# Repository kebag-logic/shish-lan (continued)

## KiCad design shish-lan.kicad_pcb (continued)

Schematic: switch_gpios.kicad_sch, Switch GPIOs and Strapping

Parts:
J13, J14: SMA; SMA_Right_Angle; MPN RFPC-SMA27-F; Mouser 640-RFPCSMA27F; not fitted
R13, R133: 10K; R_0603; Tolerance_in_pct 5; MPN CRCW060310K0JNEC; Mouser 71-CRCW060310K0JNEC
R17, R25, R92, R126, R127, R128, R129, R135, R136: 0R; R_0603; Tolerance_in_pct 5; MPN RC0603JR-070RP; Mouser 603-RC0603JR-070RP
R18, R21, R22, R93, R98, R119, R130, R131, R132, R134: 0R; R_0603; Tolerance_in_pct 5; MPN RC0603JR-070RP; Mouser 603-RC0603JR-070RP; not fitted
R69: 1K5; R_0603; Tolerance_in_pct 5; MPN AC0603JR-071K5L; Mouser 603-AC0603JR-071K5L
R113, R114, R115, R116, R117, R118: 22R; R_0603; Tolerance_in_pct 1; MPN RC0603FR-1022RL; Mouser 603-RC0603FR-1022RL
TP21, TP22, TP24, TP25, TP26, TP27: TestPoint
U1: LAN96455F-I/8MW; TQFP-128_14x14mm_P0.4mm; MPN LAN96455F-I/8MW; Mouser 579-LAN96455FI8MW

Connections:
/controller/MIIM0_STM_SWITCH.SLV_MDC: R17.1; also elsewhere on the board
/controller/MIIM0_STM_SWITCH.SLV_MDIO: R25.1; also elsewhere on the board
/controller/RGMII0_SWITCH_STM.RXCTL-CRS_DV: U1.74 (GPIO_21/RGMII0_RXCTL-CRS_DV); also elsewhere on the board
/controller/RGMII0_SWITCH_STM.RXD0: U1.80 (GPIO_16/RGMII0_RXD0); also elsewhere on the board
/controller/RGMII0_SWITCH_STM.RXD1: U1.79 (GPIO_17/RGMII0_RXD1); also elsewhere on the board
/controller/RGMII0_SWITCH_STM.RXD2: U1.78 (GPIO_18/RGMII0_RXD2-RXER); also elsewhere on the board
/controller/RGMII0_SWITCH_STM.RXD3: U1.76 (GPIO_19/RGMII0_RXD3); also elsewhere on the board
/controller/RGMII0_SWITCH_STM.RX_CLK: U1.75 (GPIO_20/RGMII0_RXC-REFCLK); also elsewhere on the board
/controller/RGMII0_SWITCH_STM.TXC-REFCLK: R118.1; also elsewhere on the board
/controller/RGMII0_SWITCH_STM.TXCTL-DX_DV: R117.1; also elsewhere on the board
/controller/RGMII0_SWITCH_STM.TXD0: R116.1; also elsewhere on the board
/controller/RGMII0_SWITCH_STM.TXD1: R115.1; also elsewhere on the board
/controller/RGMII0_SWITCH_STM.TXD2: R114.1; also elsewhere on the board
/controller/RGMII0_SWITCH_STM.TXD3: R113.1; also elsewhere on the board
/controller/SPI2_STM_SWITCH.CLK: R18.1, TP27.1 (1_1); also elsewhere on the board
/controller/SPI2_STM_SWITCH.MISO: R22.1, TP25.1 (1_1); also elsewhere on the board
/controller/SPI2_STM_SWITCH.MOSI: R21.1, TP24.1 (1_1); also elsewhere on the board
/controller/SPI2_STM_SWITCH.nCS: TP26.1 (1_1), U1.98 (GPIO_2/SI_nCS/SI_SLV_nCS/I2C1_SDA/-/-/-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); also elsewhere on the board
/switch/IRQ0_SWITCH_TO_STM: R92.1; also elsewhere on the board
/switch/switch_gpios/BOOT_MODE0: R116.2, U1.70 (GPIO_24/RGMII0_TXD0/-/-/-/-/-/-|BOOT_MO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); also elsewhere on the board
/switch/switch_gpios/BOOT_MODE1: R115.2, U1.68 (GPIO_25/RGMII0_TXD1/-/-/-/-/-/-|BOOT_MO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); also elsewhere on the board
/switch/switch_gpios/BOOT_MODE2: R114.2, U1.67 (GPIO_26/RGMII0_TXD2/-/-/-/-/-/-|BOOT_MO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); also elsewhere on the board
/switch/switch_gpios/CUPHY_MODE: U1.82 (GPIO_14/RGMII1_TXD2/I2C0_SCL12/-/PTP2/-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); also elsewhere on the board
/switch/switch_gpios/E2E_CLOCK_EN: U1.87 (GPIO_10/RGMII1_TXC-REFCLK/I2C0_SCL8/RCL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); also elsewhere on the board
/switch/switch_gpios/EEE_EN: R98.2, U1.85 (GPIO_12/RGMII1_TXD0/I2C0_SCL10/MIIM1_MD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); also elsewhere on the board
/switch/switch_gpios/EEPROM_SIZE: R92.2, R93.2, U1.60 (GPIO_33/PTP3/IRQ0/|EEPROM_SIZE); also elsewhere on the board
/switch/switch_gpios/FLOW_EN: U1.86 (GPIO_11/RGMII1_TXCTL-TX_DV/I2C0_SCL9/MI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); also elsewhere on the board
/switch/switch_gpios/GPIO_MODE0: R126.2, U1.41 (GPIO_36/PTP0/PHY3_LED0/PHY2_LED0/-/MAC_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); also elsewhere on the board
/switch/switch_gpios/GPIO_MODE1: R127.2, U1.40 (GPIO_37/PTP1/PHY3_LED1/PHY1_LED0/-/MAC_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); also elsewhere on the board
/switch/switch_gpios/JTAG_ENB: U1.43 (GPIO_34/RCLK0/PHY4_LED0/PHY4_LED0/-/-/-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); also elsewhere on the board
/switch/switch_gpios/JTAG_SWITCH.TCK: R131.1
/switch/switch_gpios/JTAG_SWITCH.TDI: R130.1
/switch/switch_gpios/JTAG_SWITCH.TDO: R132.1
/switch/switch_gpios/JTAG_SWITCH.TMS: R134.1
/switch/switch_gpios/LED_MODE: U1.83 (GPIO_13/RGMII1_TXD1/I2C0_SCL11/-/PTP1/M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); also elsewhere on the board
/switch/switch_gpios/LOOP_EN: U1.42 (GPIO_35/RCLK1/PHY4_LED1/PHY3_LED0/-/MAC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); also elsewhere on the board
/switch/switch_gpios/MGMT_MODE0: R113.2, U1.66 (GPIO_27/RGMII0_TXD3/-/-/-/-/-/-|MGMT_MO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); also elsewhere on the board
/switch/switch_gpios/MGMT_MODE1: R119.2, U1.65 (GPIO_28/RCLK0/MIIM0_MDC/-/-/-/-/-|MGMT_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); also elsewhere on the board
/switch/switch_gpios/PHY0_LED0: R133.2, U1.33 (GPIO_42/SI_nCS/PHY0_LED0/SG0_DI/IRQ2/MA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); also elsewhere on the board
/switch/switch_gpios/PHY0_LED1: R134.2, U1.31 (GPIO_43/SI_CLK/PHY0_LED1/SG0_LD/IRQ3/MA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); also elsewhere on the board
/switch/switch_gpios/PHY1_LED0: R136.1; also elsewhere on the board
/switch/switch_gpios/PHY1_LED1: R135.1; also elsewhere on the board
/switch/switch_gpios/PHY2_LED0: R128.1; also elsewhere on the board
/switch/switch_gpios/PHY2_LED1: R129.1; also elsewhere on the board
/switch/switch_gpios/PHY3_LED0: R126.1; also elsewhere on the board
/switch/switch_gpios/PHY3_LED1: R127.1; also elsewhere on the board
/switch/switch_gpios/PTP0: J14.1 (In), U1.63 (GPIO_30/PTP0/I2C0_SDA/UART_RXD/-/-/-/-)
/switch/switch_gpios/PTP1: U1.62 (GPIO_31/PTP1/I2C0_SCL0/UART_TXD/-/-/-/-)
/switch/switch_gpios/PTP2: U1.61 (GPIO_32/PTP2/I2C0_SCL1/-/-/-/-/-)
/switch/switch_gpios/PTP3: R93.1
/switch/switch_gpios/SD_125M: R117.2, U1.71 (GPIO_23/RGMII0_TXCTL-TX_DV/-/-/-/-/-/-|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); also elsewhere on the board
/switch/switch_gpios/SD_MODE0: R129.2, R130.2, U1.36 (GPIO_39/UART_TXD/PHY2_LED1/-/-/MAC_LED4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); also elsewhere on the board
/switch/switch_gpios/SD_MODE1: R131.2, R136.2, U1.35 (GPIO_40/SI_DI/PHY1_LED0/SG0_CLK/-/MAC_L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); also elsewhere on the board
/switch/switch_gpios/SFP_EN: U1.81 (GPIO_15/RGMII1_TXD3/I2C0_SCL13/-/PTP3/-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); also elsewhere on the board
/switch/switch_gpios/SGPIO_EN: R118.2, U1.72 (GPIO_22/RGMII0_TXC-REFCLK/-/-/-/-/-/-|G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); also elsewhere on the board
/switch/switch_gpios/SYNCE_0: R119.1; also elsewhere on the board
/switch/switch_gpios/SYNCE_1: U1.64 (GPIO_29/RCLK1/MIIM0_MDIO/-/-/-/-/-); also elsewhere on the board
/switch/switch_gpios/XMII_MODE0: R132.2, R135.2, U1.34 (GPIO_41/SI_DO/PHY1_LED1/SG0_DO/IRQ1/MAC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); also elsewhere on the board
/switch/switch_gpios/XMII_MODE1: R128.2, U1.38 (GPIO_38/-/PHY2_LED0/PHY0_LED0/-/MAC_LED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); also elsewhere on the board
unnamed: J13.1 (In), R98.1
unnamed: R13.1, R21.2, U1.100 (GPIO_0/SI_DI/SI_SLV_DI/I2C_SLV_SDA/MIIM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)
unnamed: R17.2, R22.2, TP21.1 (1_1), U1.99 (GPIO_1/SI_DO/SI_SLV_DO/I2C_SLV_SCL/MIIM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)
unnamed: R18.2, R25.2, R69.2, TP22.1 (1_1), U1.97 (GPIO_3/SI_CLK//SI_SLV_CLK/I2C1_SCL/MIIM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)

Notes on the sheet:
Checklist * Pinouts [ AM 2026-12-21 OK ] * Element correctness (KL) [ AM 2026-12-21 OK ] * Connections [ AM 2026-12-21 OK ]
We leave the option to use either the SPI or the MDIO bus. If the MDIO is used, remove R69 and R13.

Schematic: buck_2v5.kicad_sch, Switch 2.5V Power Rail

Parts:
C96, C100: 10u; C_0603; Voltage_in_V 25; Tolerance_in_pct 20; MPN CL10A106MA8NRNC; Mouser 187-CL10A106MA8NRNC; not fitted
C97, C101, C102, C107, C108: 10u; C_0603; Voltage_in_V 25; Tolerance_in_pct 20; MPN CL10A106MA8NRNC; Mouser 187-CL10A106MA8NRNC
C99: 10p; C_0603; Voltage_in_V 25; Tolerance_in_pct 5; MPN CC0603JRNPO8BN100; Mouser 603-CC0603JRNP8BN100
C103: 10n; C_0603; Voltage_in_V 50; Tolerance_in_pct 10; MPN CL10B103KB8WPND; Mouser 187-CL10B103KB8WPND; not fitted
D2: LED_{color}_{U_F}_{I_F}; LED_0603; MPN LTST-C194KRKT; Mouser 859-LTST-C194KRKT
J17: Header_02x01_2.54mm_0mm_Straight; 02x01_2.54mm_Header; MPN 87224-2; Mouser 571-872242
L3: 3u3; EXLA1V0603; Tolerance_in_pct 20; MPN EXLA1V0603-3R3-R; Digikey 283-EXLA1V0603-3R3-RCT-ND
R19: 31K6; R_0603; Tolerance_in_pct 1; MPN CRCW060331K6FKEA; Mouser 71-CRCW0603-31.6K-E3
R85: 10K; R_0603; Tolerance_in_pct 1; MPN RC0603FR-0710KL; Mouser 603-RC0603FR-0710KL
R95: 1K5; R_0603; Tolerance_in_pct 5; MPN AC0603JR-071K5L; Mouser 603-AC0603JR-071K5L
R99: 10K; R_0603; Tolerance_in_pct 5; MPN CRCW060310K0JNEC; Mouser 71-CRCW060310K0JNEC; not fitted
TP28, TP29, TP30, TP31: TestPoint
U3: TPS564257DRLR; SOT-563; MPN TPS564257DRLR; Mouser 595-TPS564257DRLR

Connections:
/5-12V_INPUT: C100.1, C101.1, C102.1, TP29.1 (1_1), U3.1 (VIN); also elsewhere on the board
/switch/2V5_BUCK-OUT: C96.1, C97.1, C107.1, J17.1, TP28.1 (1_1); also elsewhere on the board
unnamed: D2.2 (A), R95.2
unnamed: D2.1 (K), TP30.1 (1_1), U3.4 (PG)
unnamed: C99.1, C108.1, J17.2, L3.2, R19.1
unnamed: C99.2, R19.2, R85.1, U3.6 (FB)
unnamed: L3.1, U3.2 (SW)

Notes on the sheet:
Based on WEBENCH design: https://drive.google.com/file/d/1STtModBE37J_lW2Zfq6PtjpJq2d4hOYi/view?usp=drive_link
Checklist * Pinouts [ AM OK - 2026-12-21 ] * Element correctness [ AM OK - 2026-12-21 ] * Connections [ AM OK - 2026-12-21 ]
Documentation found here: https://www.ti.com/product/TPS564257
Generation of the 2.5V for PHYs

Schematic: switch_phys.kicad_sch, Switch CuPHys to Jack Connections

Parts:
R70: 6K04; R_0603; Tolerance_in_pct 1; MPN RMCF0603FT6K04; Mouser 708-RMCF0603FT6K04
U1: LAN96455F-I/8MW; TQFP-128_14x14mm_P0.4mm; MPN LAN96455F-I/8MW; Mouser 579-LAN96455FI8MW

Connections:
/switch/switch_phys/RJ45_Connector_Port0/TRD1+_0: U1.102 (P0.A_P); also elsewhere on the board
/switch/switch_phys/RJ45_Connector_Port0/TRD1-_0: U1.103 (P0.A_N); also elsewhere on the board
/switch/switch_phys/RJ45_Connector_Port0/TRD2+_0: U1.105 (P0.B_P); also elsewhere on the board
/switch/switch_phys/RJ45_Connector_Port0/TRD2-_0: U1.106 (P0.B_N); also elsewhere on the board
/switch/switch_phys/RJ45_Connector_Port0/TRD3+_0: U1.108 (P0.C_P); also elsewhere on the board
/switch/switch_phys/RJ45_Connector_Port0/TRD3-_0: U1.109 (P0.C_N); also elsewhere on the board
/switch/switch_phys/RJ45_Connector_Port0/TRD4+_0: U1.110 (P0.D_P); also elsewhere on the board
/switch/switch_phys/RJ45_Connector_Port0/TRD4-_0: U1.111 (P0.D_N); also elsewhere on the board
/switch/switch_phys/RJ45_Connector_Port1/TRD1+_1: U1.112 (P1.A_P); also elsewhere on the board
/switch/switch_phys/RJ45_Connector_Port1/TRD1-_1: U1.113 (P1.A_N); also elsewhere on the board
/switch/switch_phys/RJ45_Connector_Port1/TRD2+_1: U1.114 (P1.B_P); also elsewhere on the board
/switch/switch_phys/RJ45_Connector_Port1/TRD2-_1: U1.115 (P1.B_N); also elsewhere on the board
/switch/switch_phys/RJ45_Connector_Port1/TRD3+_1: U1.117 (P1.C_P); also elsewhere on the board
/switch/switch_phys/RJ45_Connector_Port1/TRD3-_1: U1.118 (P1.C_N); also elsewhere on the board
/switch/switch_phys/RJ45_Connector_Port1/TRD4+_1: U1.120 (P1.D_P); also elsewhere on the board
/switch/switch_phys/RJ45_Connector_Port1/TRD4-_1: U1.121 (P1.D_N); also elsewhere on the board
/switch/switch_phys/RJ45_Connector_Port2/TRD1+_2: U1.1 (P2.A_P); also elsewhere on the board
/switch/switch_phys/RJ45_Connector_Port2/TRD1-_2: U1.2 (P2.A_N); also elsewhere on the board
/switch/switch_phys/RJ45_Connector_Port2/TRD2+_2: U1.4 (P2.B_P); also elsewhere on the board
/switch/switch_phys/RJ45_Connector_Port2/TRD2-_2: U1.5 (P2.B_N); also elsewhere on the board
/switch/switch_phys/RJ45_Connector_Port2/TRD3+_2: U1.7 (P2.C_P); also elsewhere on the board
/switch/switch_phys/RJ45_Connector_Port2/TRD3-_2: U1.8 (P2.C_N); also elsewhere on the board
/switch/switch_phys/RJ45_Connector_Port2/TRD4+_2: U1.9 (P2.D_P); also elsewhere on the board
/switch/switch_phys/RJ45_Connector_Port2/TRD4-_2: U1.10 (P2.D_N); also elsewhere on the board
/switch/switch_phys/RJ45_Connector_Port3/TRD1+_3: U1.11 (P3.A_P); also elsewhere on the board
/switch/switch_phys/RJ45_Connector_Port3/TRD1-_3: U1.12 (P3.A_N); also elsewhere on the board
/switch/switch_phys/RJ45_Connector_Port3/TRD2+_3: U1.13 (P3.B_P); also elsewhere on the board
/switch/switch_phys/RJ45_Connector_Port3/TRD2-_3: U1.14 (P3.B_N); also elsewhere on the board
/switch/switch_phys/RJ45_Connector_Port3/TRD3+_3: U1.17 (P3.C_P); also elsewhere on the board
/switch/switch_phys/RJ45_Connector_Port3/TRD3-_3: U1.18 (P3.C_N); also elsewhere on the board
/switch/switch_phys/RJ45_Connector_Port3/TRD4+_3: U1.19 (P3.D_P); also elsewhere on the board
/switch/switch_phys/RJ45_Connector_Port3/TRD4-_3: U1.20 (P3.D_N); also elsewhere on the board
unnamed: R70.1, U1.127 (ISET)

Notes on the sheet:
Checklist * Pinouts [ AM OK - 2026-12-21 ] * Element correctness [ AM OK - 2026-12-21 ] * Connections [ AM OK - 2026-12-21 ]
The assumption, for the LEDS is that the VDD_IO will be 3.3V not 1.8V, not 2.5V

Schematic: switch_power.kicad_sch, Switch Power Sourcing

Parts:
C1, C18, C19, C20, C21: 100n; C_0603; Voltage_in_V 50; Tolerance_in_pct 10; MPN CL10B104KB8NNNC; Mouser 187-CL10B104KB8NNNC
C106: 10n; C_0603; Voltage_in_V 50; Tolerance_in_pct 10; MPN CL10B103KB8WPND; Mouser 187-CL10B103KB8WPND; not fitted
FB1, FB2, FB3, FB4, FB5: 33R; FB_0603; MPN BLM18PG330SN1D; Mouser 81-BLM18PG330SN1D
R71: 10R; R_0603; Tolerance_in_pct 0.1; MPN RNCE0603BTE10R0; Mouser 708-RNCE0603BTE10R0
R72, R73: 0R; R_0603; Tolerance_in_pct 5; MPN RC0603JR-070RP; Mouser 603-RC0603JR-070RP
R81: 10K; R_0603; Tolerance_in_pct 5; MPN CRCW060310K0JNEC; Mouser 71-CRCW060310K0JNEC
R88, R120, R121: 0R; R_2512; Tolerance_in_pct 5; MPN CRF2512-J/-000ELF; Mouser 652-CRF2512-J-000ELF; not fitted
TP4, TP5, TP6, TP7, TP8, TP9, TP19, TP20: TestPoint
U1: LAN96455F-I/8MW; TQFP-128_14x14mm_P0.4mm; MPN LAN96455F-I/8MW; Mouser 579-LAN96455FI8MW

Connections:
/switch/1V15_BUCK-OUT: R121.1; also elsewhere on the board
/switch/2V5_BUCK-OUT: R120.1; also elsewhere on the board
/switch/nRST_STM_TO_SWITCH: C106.1, R81.1, TP20.1 (1_1), U1.101 (nRST); also elsewhere on the board
/switch/switch_power/1V15_PWR_SWITCH: C19.1, C20.1, FB1.1, FB2.1, FB3.1, R121.2, TP8.1 (1_1), U1.37 (VDD), U1.59 (VDD), U1.73 (VDD), U1.88 (VDD), U1.122 (VDD); also elsewhere on the board
/switch/switch_power/2V5_PWR_SWITCH: C1.1, C18.1, FB4.1, FB5.1, R120.2
/switch/switch_power/VDDIO: R88.2, U1.32 (VDD_IO_E), U1.39 (VDD_IO_E), U1.58 (VDD_IO_D), U1.69 (VDD_IO_C), U1.77 (VDD_IO_C), U1.84 (VDD_IO_B), U1.92 (VDD_IO_B), U1.96 (VDD_IO_A); also elsewhere on the board
/switch/switch_power/VDDIO_PHY_AH: FB4.2, TP6.1 (1_1), U1.6 (VDD_AH), U1.16 (VDD_AH), U1.25 (VDD_AH), U1.107 (VDD_AH), U1.116 (VDD_AH), U1.128 (VDD_AH); also elsewhere on the board
/switch/switch_power/VDDIO_PHY_AHS: FB5.2, TP7.1 (1_1), U1.44 (VDD_AHS), U1.52 (VDD_AHS); also elsewhere on the board
/switch/switch_power/VDD_PHYS: FB3.2, TP4.1 (1_1), U1.3 (VDD_AL), U1.15 (VDD_AL), U1.28 (VDD_AL), U1.104 (VDD_AL), U1.119 (VDD_AL); also elsewhere on the board
/switch/switch_power/VDD_SERDES: FB2.2, TP5.1 (1_1), U1.47 (VDD_ALS0), U1.54 (VDD_ALS1); also elsewhere on the board
/switch/switch_power/xtal_switch/Pin1: R73.1, TP9.1 (1_1); also elsewhere on the board
/switch/switch_power/xtal_switch/Pin2: R72.1, TP19.1 (1_1); also elsewhere on the board
unnamed: FB1.2, R71.1
unnamed: C21.2, U1.125 (RTN_PLL)
unnamed: C21.1, R71.2, U1.126 (VDD_PLL)
unnamed: R73.2, U1.124 (XI)
unnamed: R72.2, U1.123 (XO)

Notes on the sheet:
WARNING: Make sure that the LEDS in the PHY part are connected to the right power
The voltage selected (2.5V or 3.3V) must also be used on the VDD_AHS supply.
Checklist * Pinouts [ AM OK - 2026-12-21 ] * Element correctness [ AM OK - 2026-12-21 ] * Connections [ AM OK - 2026-12-21 ]
VDD on the Domain D has to be 3.3V

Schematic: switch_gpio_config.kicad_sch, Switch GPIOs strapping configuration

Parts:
R14, R35, R37, R41, R44, R52, R56, R68: 10K; R_0603; Tolerance_in_pct 5; MPN CRCW060310K0JNEC; Mouser 71-CRCW060310K0JNEC
R26, R27, R28, R29, R30, R31, R32, R33, R34, R36, R38, R39, R40, R42, R43, R45, R46, R47, R48, R49, R50, R51, R53, R54, R55, R57, R58, R59, R60, R61, R62, R63, R64, R65, R66, R67: 10K; R_0603; Tolerance_in_pct 5; MPN CRCW060310K0JNEC; Mouser 71-CRCW060310K0JNEC; not fitted

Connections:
/switch/switch_gpios/BOOT_MODE0: R30.2, R52.1; also elsewhere on the board
/switch/switch_gpios/BOOT_MODE1: R34.2, R68.1; also elsewhere on the board
/switch/switch_gpios/BOOT_MODE2: R35.1, R65.2; also elsewhere on the board
/switch/switch_gpios/CUPHY_MODE: R40.2, R60.1; also elsewhere on the board
/switch/switch_gpios/E2E_CLOCK_EN: R47.2, R51.1; also elsewhere on the board
/switch/switch_gpios/EEE_EN: R49.1, R58.2; also elsewhere on the board
/switch/switch_gpios/EEPROM_SIZE: R42.1, R63.2; also elsewhere on the board
/switch/switch_gpios/FLOW_EN: R45.2, R64.1; also elsewhere on the board
/switch/switch_gpios/GPIO_MODE0: R39.1, R57.2; also elsewhere on the board
/switch/switch_gpios/GPIO_MODE1: R38.1, R59.2; also elsewhere on the board
/switch/switch_gpios/JTAG_ENB: R41.2, R53.1; also elsewhere on the board
/switch/switch_gpios/LED_MODE: R48.2, R50.1; also elsewhere on the board
/switch/switch_gpios/LOOP_EN: R28.1, R43.2; also elsewhere on the board
/switch/switch_gpios/MGMT_MODE0: R55.2, R56.1; also elsewhere on the board
/switch/switch_gpios/MGMT_MODE1: R14.2, R54.1; also elsewhere on the board
/switch/switch_gpios/SD_125M: R37.1, R67.2; also elsewhere on the board
/switch/switch_gpios/SD_MODE0: R29.2, R31.1; also elsewhere on the board
/switch/switch_gpios/SD_MODE1: R33.1, R36.2; also elsewhere on the board
/switch/switch_gpios/SFP_EN: R46.1, R61.2; also elsewhere on the board
/switch/switch_gpios/SGPIO_EN: R44.1, R62.2; also elsewhere on the board
/switch/switch_gpios/XMII_MODE0: R26.2, R66.1; also elsewhere on the board
/switch/switch_gpios/XMII_MODE1: R27.2, R32.1; also elsewhere on the board

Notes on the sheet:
*0: Disable EEE on CuPHY ports 1: Enable EEE on CuPHY ports
MANAGED CONFIGURATION STRAPS
*0: GPIOs will be used to control SFP signals 1: SGPIOS will be used to control SFP signals
Enables a 125 MHz reference clock input to SerDes Note: If SD_125M is strapped high, SGPIO_EN must be strapped low.
0: Single color mode (one LED signaling link-up and one led signaling activity) *1: Tri-color mode (two LEDs to indicate link-up with different color depending on link speed, LEDs blinking with activity)
*0: 16-bit addressing 1: 8-bit addressing
Management Interface Mode Selector 0: UART CLI 1: I2C client *2: MIIM client 3: SPI client
*0: Disable flow control 1: Enable flow control
*0: SGMII (1G, 2.5G) 1: SFP (-X, -KX, -FX)
*0: Disable end-to-end transparent clock 1: Enable end-to-end transparent clock
0: Auto negotiation, Auto MDI-X - all advertised *1: Auto negotiation, Auto MDI-X - 100FD/HD, 10FD/HD advertised
*0: Disable loop prevention 1: Enable loop prevention
Note: If JTAG is enabled, configuration strap BOOT_MODE0 selects: 0: DFT TAP controller 1: SerDes TAP controller 0: Enable JTAG *1: Disable JTAG
Each strap number controls a corresponding RGMII interface number. 0: RGMII *1: RMII
*0: Disable 2.5G detect 1: Enable 2.5G detect
0: Mode A (2x RGMII, 1-2x SGMII) 1: Mode B (1x QSGMII, 0x SGMII, 0-1x RGMII) 2: Mode C (2x RGMII, 0x SGMII) *3: Mode D (0-1x RGMII, 0-2x SGMII)
Boot Mode Selector Note: Unmanaged modes are selected using options 3, 4, 5, 6, or 7. *0: [Managed] No boot --> Need management interface to work 1: RESERVED 2: RESERVED 3: [Unmanaged] ROM boot. 4: [Unmanaged] ROM + I2C table boot. 5: [Unmanaged] ROM + SPI table boot. 6: [Unmanaged] ROM + VRAP port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

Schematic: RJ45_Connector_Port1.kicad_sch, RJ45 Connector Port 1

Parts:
C3, C8, C9, C10: 100n; C_0603; Voltage_in_V 50; Tolerance_in_pct 10; MPN CL10B104KB8NNNC; Mouser 187-CL10B104KB8NNNC
J1: RJ45_0826-1X4T-43-F; BEL_0826-1X4T-43-F; MPN 0826-1X4T-43-F; Mouser 530-0826-1X4T-43-F
R1, R2, R11: 1K; R_0603; Tolerance_in_pct 5; MPN CRGCQ0603J1K0; Mouser 279-CRGCQ0603J1K0

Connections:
/switch/switch_gpios/PHY1_LED0: R2.1; also elsewhere on the board
/switch/switch_gpios/PHY1_LED1: J1.15_2; also elsewhere on the board
/switch/switch_phys/RJ45_Connector_Port1/TRD1+_1: J1.11_2 (TRD1+_2); also elsewhere on the board
/switch/switch_phys/RJ45_Connector_Port1/TRD1-_1: J1.10_2 (TRD1-_2); also elsewhere on the board
/switch/switch_phys/RJ45_Connector_Port1/TRD2+_1: J1.4_2 (TRD2+_2); also elsewhere on the board
/switch/switch_phys/RJ45_Connector_Port1/TRD2-_1: J1.5_2 (TRD2-_2); also elsewhere on the board
/switch/switch_phys/RJ45_Connector_Port1/TRD3+_1: J1.3_2 (TRD3+_2); also elsewhere on the board
/switch/switch_phys/RJ45_Connector_Port1/TRD3-_1: J1.2_2 (TRD3-_2); also elsewhere on the board
/switch/switch_phys/RJ45_Connector_Port1/TRD4+_1: J1.8_2 (TRD4+_2); also elsewhere on the board
/switch/switch_phys/RJ45_Connector_Port1/TRD4-_1: J1.9_2 (TRD4-_2); also elsewhere on the board
unnamed: J1.13_2, R2.2
unnamed: J1.16_2, R1.2, R11.1
unnamed: C3.2, J1.12_2 (TRCT1_2)
unnamed: C8.2, J1.6_2 (TRCT2_2)
unnamed: C9.2, J1.1_2 (TRCT3_2)
unnamed: C10.2, J1.7_2 (TRCT4_2)

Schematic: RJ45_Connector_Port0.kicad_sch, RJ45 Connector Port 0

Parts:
C4, C5, C6, C7: 100n; C_0603; Voltage_in_V 50; Tolerance_in_pct 10; MPN CL10B104KB8NNNC; Mouser 187-CL10B104KB8NNNC
J1: RJ45_0826-1X4T-43-F; BEL_0826-1X4T-43-F; MPN 0826-1X4T-43-F; Mouser 530-0826-1X4T-43-F
R5, R6, R7: 1K; R_0603; Tolerance_in_pct 5; MPN CRGCQ0603J1K0; Mouser 279-CRGCQ0603J1K0

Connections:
/switch/switch_gpios/PHY0_LED0: R6.1; also elsewhere on the board
/switch/switch_gpios/PHY0_LED1: J1.15_1; also elsewhere on the board
/switch/switch_phys/RJ45_Connector_Port0/TRD1+_0: J1.11_1 (TRD1+_1); also elsewhere on the board
/switch/switch_phys/RJ45_Connector_Port0/TRD1-_0: J1.10_1 (TRD1-_1); also elsewhere on the board
/switch/switch_phys/RJ45_Connector_Port0/TRD2+_0: J1.4_1 (TRD2+_1); also elsewhere on the board
/switch/switch_phys/RJ45_Connector_Port0/TRD2-_0: J1.5_1 (TRD2-_1); also elsewhere on the board
/switch/switch_phys/RJ45_Connector_Port0/TRD3+_0: J1.3_1 (TRD3+_1); also elsewhere on the board
/switch/switch_phys/RJ45_Connector_Port0/TRD3-_0: J1.2_1 (TRD3-_1); also elsewhere on the board
/switch/switch_phys/RJ45_Connector_Port0/TRD4+_0: J1.8_1 (TRD4+_1); also elsewhere on the board
/switch/switch_phys/RJ45_Connector_Port0/TRD4-_0: J1.9_1 (TRD4-_1); also elsewhere on the board
unnamed: J1.13_1, R6.2
unnamed: J1.16_1, R5.2, R7.1
unnamed: C4.2, J1.12_1 (TRCT1_1)
unnamed: C5.2, J1.6_1 (TRCT2_1)
unnamed: C6.1, J1.1_1 (TRCT3_1)
unnamed: C7.2, J1.7_1 (TRCT4_1)

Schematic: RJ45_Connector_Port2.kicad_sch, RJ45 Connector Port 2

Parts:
C11, C12, C13, C14: 100n; C_0603; Voltage_in_V 50; Tolerance_in_pct 10; MPN CL10B104KB8NNNC; Mouser 187-CL10B104KB8NNNC
J1: RJ45_0826-1X4T-43-F; BEL_0826-1X4T-43-F; MPN 0826-1X4T-43-F; Mouser 530-0826-1X4T-43-F
R3, R4, R8: 1K; R_0603; Tolerance_in_pct 5; MPN CRGCQ0603J1K0; Mouser 279-CRGCQ0603J1K0

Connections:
/switch/switch_gpios/PHY2_LED0: R3.1; also elsewhere on the board
/switch/switch_gpios/PHY2_LED1: J1.15_3; also elsewhere on the board
/switch/switch_phys/RJ45_Connector_Port2/TRD1+_2: J1.11_3 (TRD1+_3); also elsewhere on the board
/switch/switch_phys/RJ45_Connector_Port2/TRD1-_2: J1.10_3 (TRD1-_3); also elsewhere on the board
/switch/switch_phys/RJ45_Connector_Port2/TRD2+_2: J1.4_3 (TRD2+_3); also elsewhere on the board
/switch/switch_phys/RJ45_Connector_Port2/TRD2-_2: J1.5_3 (TRD2-_3); also elsewhere on the board
/switch/switch_phys/RJ45_Connector_Port2/TRD3+_2: J1.3_3 (TRD3+_3); also elsewhere on the board
/switch/switch_phys/RJ45_Connector_Port2/TRD3-_2: J1.2_3 (TRD3-_3); also elsewhere on the board
/switch/switch_phys/RJ45_Connector_Port2/TRD4+_2: J1.8_3 (TRD4+_3); also elsewhere on the board
/switch/switch_phys/RJ45_Connector_Port2/TRD4-_2: J1.9_3 (TRD4-_3); also elsewhere on the board
unnamed: J1.13_3, R3.2
unnamed: J1.16_3, R4.1, R8.2
unnamed: C11.1, J1.12_3 (TRCT1_3)
unnamed: C12.2, J1.6_3 (TRCT2_3)
unnamed: C13.2, J1.1_3 (TRCT3_3)
unnamed: C14.2, J1.7_3 (TRCT4_3)

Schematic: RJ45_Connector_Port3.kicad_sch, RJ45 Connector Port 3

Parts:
C2, C15, C16, C17: 100n; C_0603; Voltage_in_V 50; Tolerance_in_pct 10; MPN CL10B104KB8NNNC; Mouser 187-CL10B104KB8NNNC
J1: RJ45_0826-1X4T-43-F; BEL_0826-1X4T-43-F; MPN 0826-1X4T-43-F; Mouser 530-0826-1X4T-43-F
R9, R10, R12: 1K; R_0603; Tolerance_in_pct 5; MPN CRGCQ0603J1K0; Mouser 279-CRGCQ0603J1K0

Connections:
/switch/switch_gpios/PHY3_LED0: R12.1; also elsewhere on the board
/switch/switch_gpios/PHY3_LED1: J1.15_4; also elsewhere on the board
/switch/switch_phys/RJ45_Connector_Port3/TRD1+_3: J1.11_4 (TRD1+_4); also elsewhere on the board
/switch/switch_phys/RJ45_Connector_Port3/TRD1-_3: J1.10_4 (TRD1-_4); also elsewhere on the board
/switch/switch_phys/RJ45_Connector_Port3/TRD2+_3: J1.4_4 (TRD2+_4); also elsewhere on the board
/switch/switch_phys/RJ45_Connector_Port3/TRD2-_3: J1.5_4 (TRD2-_4); also elsewhere on the board
/switch/switch_phys/RJ45_Connector_Port3/TRD3+_3: J1.3_4 (TRD3+_4); also elsewhere on the board
/switch/switch_phys/RJ45_Connector_Port3/TRD3-_3: J1.2_4 (TRD3-_4); also elsewhere on the board
/switch/switch_phys/RJ45_Connector_Port3/TRD4+_3: J1.8_4 (TRD4+_4); also elsewhere on the board
/switch/switch_phys/RJ45_Connector_Port3/TRD4-_3: J1.9_4 (TRD4-_4); also elsewhere on the board
unnamed: J1.13_4, R12.2
unnamed: J1.16_4, R9.2, R10.1
unnamed: C2.2, J1.12_4 (TRCT1_4)
unnamed: C15.2, J1.6_4 (TRCT2_4)
unnamed: C16.2, J1.1_4 (TRCT3_4)
unnamed: C17.2, J1.7_4 (TRCT4_4)

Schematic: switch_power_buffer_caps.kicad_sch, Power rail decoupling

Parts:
C25, C27, C28, C29, C30, C31, C32, C33, C34, C35, C36, C37, C38, C39, C40, C41, C42, C43, C44, C45, C46, C47, C48, C49, C50, C51, C52, C53, C54, C55, C56, C57, C58, C59, C60, C61, C62, C63, C64, C65, C66, C67, C68, C69: 10u; C_0603; Voltage_in_V 25; Tolerance_in_pct 20; MPN CL10A106MA8NRNC; Mouser 187-CL10A106MA8NRNC

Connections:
/switch/switch_power/1V15_PWR_SWITCH: C25.1, C41.1, C42.1, C43.1, C44.1, C45.1, C46.1, C47.1, C48.1, C49.1, C50.1, C51.1, C52.1, C53.1, C54.1, C55.1, C56.1, C57.1; also elsewhere on the board
/switch/switch_power/VDDIO: C38.1, C39.1, C40.1, C58.1, C59.1, C60.1, C61.1; also elsewhere on the board
/switch/switch_power/VDDIO_PHY_AH: C30.1, C31.1; also elsewhere on the board
/switch/switch_power/VDDIO_PHY_AHS: C27.1, C28.1; also elsewhere on the board
/switch/switch_power/VDD_PHYS: C29.1, C32.1, C35.1, C36.1, C37.1, C62.1, C63.1, C64.1, C65.1, C66.1, C67.1, C68.1, C69.1; also elsewhere on the board
/switch/switch_power/VDD_SERDES: C33.1, C34.1; also elsewhere on the board

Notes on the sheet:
Put all buffer capacitors as close as possible to the power pins!

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
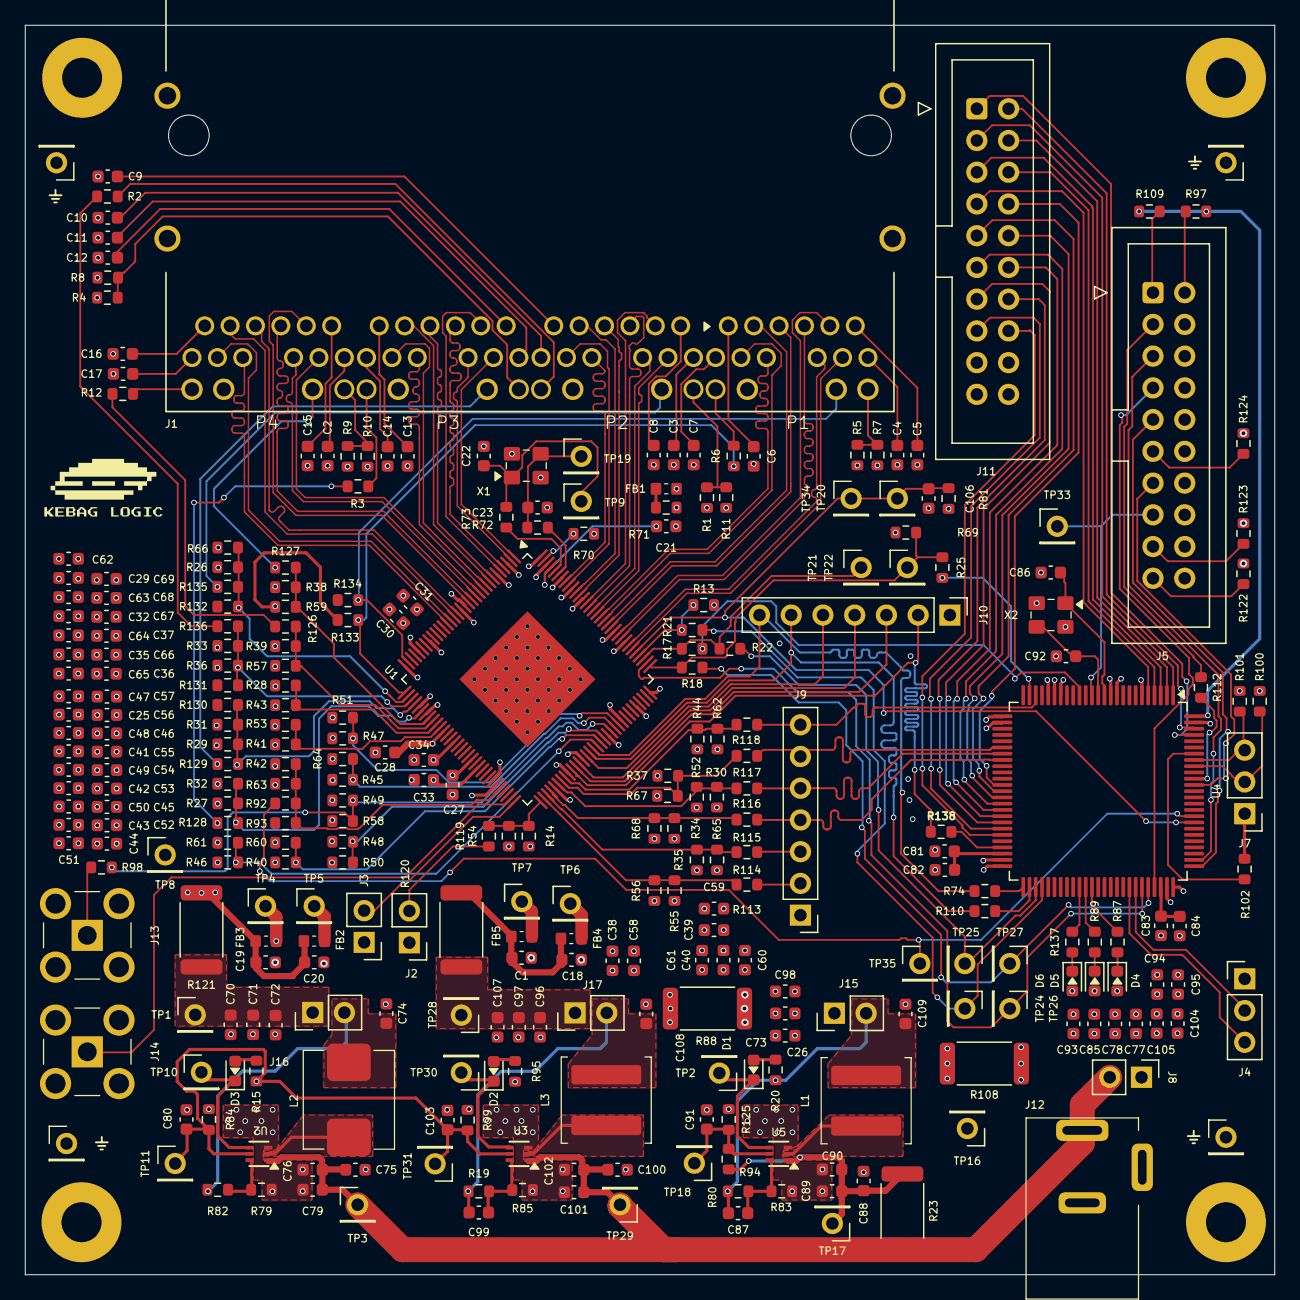
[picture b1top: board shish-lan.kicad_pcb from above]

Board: 6 copper layers, 100.0 x 100.0 mm, 304 parts (0 on the bottom side), 197 nets.

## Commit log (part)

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2025-12-14 introducing library into shish-lan
2025-12-14 Initial commit of schematics
2025-12-14 switch: adding decoupling elements
2025-12-14 updating the shish-lan
2025-12-15 CuPhy: adding ports
2025-12-18 phys: adding resistor
2025-12-18 gpios: first version of the GPIOS and strapping schematics
2025-12-18 switch: Connecting bucks/gpios/phys together
2025-12-18 updating the project
2025-12-20 schematics: fixing the voltage rail and updating the files
2025-12-20 updating the projects
2025-12-21 library: adding KL library
2025-12-21 library: update to the right library
2025-12-21 library: update to get all necessary componenents and footprints for the switch
2025-12-21 library: adding newer inductors symbols and footprints
2025-12-21 switch: finished 1st version
2025-12-21 updating the libraries
2025-12-21 minor footprint fixing
2025-12-21 remove old library
2025-12-27 updates gitignore for macOS
2025-12-27 updates kl lib
2025-12-28 review of +3V3 converter
2025-12-28 review of +2V5 converter
2025-12-28 review of +1V1 converter
2025-12-28 updates project file. Seems like this is updated on close
2026-01-05 switch: buck v1.1 -> v1.15 as requested by the switch
2026-01-05 This commit intends to fix multiple issues:
    - 1.1 -> 1.15 v buck rails
    - Revision consistently using Rev. A
    - Issue with the Switch symbol when moving library
    - Adding new footprint and symbol for 2.54mm Headers
2026-01-05 switch: annotations on switch IC and connectors
2026-01-05 fixing issue related to symbol changes, and updating components
2026-01-05 synchronising with the review branch
2026-01-06 updates test points
2026-01-06 reviews GPIOS, improves readability, clean up
2026-01-20 updates all symbols to the project only paths. My bad - sorry
2026-01-20 review of power part, cleanups, increase readability
2026-01-20 updates power sheet.
2026-01-20 cleans up PHY section and moves connectors into separate subpages
2026-01-20 moves GND to common GND symbol
2026-01-20 adds GND test points because there is always one missing for the perfect measurement
2026-01-20 fixes most critical ERC errors
2026-01-20 adds .DS_Store to gitignore. Refs: #1
2026-01-20 adds pin out documentation for stm32h7. Refs: #1
2026-01-20 Initial commit for STM power. Refs: #1
2026-01-20 updates documentation. Refs: #1
2026-01-20 updates project file and schematic. Refs: #1
2026-01-20 documentation: stm32h7: adding used orange signals
2026-01-20 documentation: stm32h7: adding RMII connection
2026-01-20 initial commit for GPIOs of STM32. Needs to resolve naming conflicts. Refs: #1
2026-01-23 adds enable pins for voltage converters. Refs: #1
2026-01-23 udpating the pinout document
2026-01-23 Adding missing I/O in red highlightings
2026-01-23 updates kicad lib
2026-01-23 adds signal naming convention
2026-01-23 updates resistors and inductor symbol in 3V3 converter
2026-01-23 updates resistors and inductor symbol in 2V5 converter
2026-01-23 updates resistors and inductor symbol in 1V15 converter
2026-01-23 renames 2V5 related nets
2026-01-23 renames 3V3 related nets
2026-01-23 renames 3V15 related nets
2026-01-23 updates IRQ0 related nets
2026-01-23 updates nRESET SWITCH related nets
2026-01-23 updates naming convention
2026-01-23 updates 25MHz clock
2026-01-23 connects SYNCE pins directly to the component
2026-01-23 updates RGMII bus to STM
2026-01-23 updates MIIM bus to STM
2026-01-23 excludes optional resistors from BOM
2026-01-23 removes todo to check nreset logic in switch
2026-01-23 aligns power blocks in the switch sheet
2026-01-23 updates buck enable, rst and IRQ to new naming scheme. Refs: #1
2026-01-24 adds crystal for STM. Refs: #1
2026-01-24 updates SPI pins. Refs: #1
2026-01-24 adds uart support. Refs:#1
2026-01-24 initial commit for jtag header. WIP. Refs: #1
2026-01-24 Adding page title, and confidential for now
2026-01-24 Adding page title, and confidential for now, fixing gpio strapping and fixing comment for gpios strappings
2026-01-24 excludes strapping resistors that are DNP from BOM
2026-01-24 excludes optional CLK_25M resistor from BOM.
2026-01-24 adds I2C Pull up and test points. Refs: #1
2026-01-24 adds boot0 configuration header. Refs: #1
2026-01-24 adds testpoint to nrst pin for easier accessibility. Refs: #1
2026-01-25 Fixing signal name for the RMII, instead of RGMII.TX_CTLR[0] call it RGMII.TXCTL-TX_DV
2026-01-25 Fixing pinout for the U(S)ART
2026-01-25 connects SPI from STM to Switch. Refs: #1
2026-01-25 connects MIIM bus from STM to Switch. Refs: #1
2026-01-25 connects RGMII1 bus between Switch and STM. Refs: #1
2026-01-25 connects nRST for switch. Refs: #1
2026-01-25 top level clean up. Refs: #1
2026-01-25 Uses crystal sheet in all places. Refs: #1
2026-01-25 modularizes xtal at STM and switch power. Refs: #1
2026-01-25 connects JTAG header. Refs: #1
2026-01-25 unused RGMII lanes are pull-up in Switch. Refs: #1
2026-01-25 renames I2C to I2C1. Refs: #1
2026-01-25 updates UART to USART. Refs: #1
2026-01-25 puts unused pins to GND as per design recommendation. Refs: #1
2026-01-25 removes pull-up todo. Refs: #1
2026-01-25 moves +3V3 converter to root. Refs: #1
2026-01-26 connects 1V15 and 2V5 to STM. Refs: #1
2026-01-26 fixes RGMII1 TX and RX resistors and duplicate name. Refs: #1
2026-01-26 fixes duplicate R13. Refs: #1
2026-01-26 removes unused en-3v3 signal from STM. Refs: #1
2026-01-26 fixes duplicate buffer caps for STM. Refs: #1
2026-01-26 fixes duplicate c83. Refs: #1
2026-01-26 fixes duplicate R85. Refs: #1
2026-01-27 fixes ERC errors in DC/DC converters
2026-01-27 updates pin headers
2026-01-27 updates components from my library misconfiguration. Refs: #1
2026-01-27 removes unused busses, adds cheaper 0R resistor, clean up to fix ERC errors. Refs: #1
2026-01-27 consistent naming for hierarchical pin and attached net. Refs: #1
2026-01-27 puts unused STM pins to NC. Refs: #1
2026-01-27 removes old ods file. Refs: #1
2026-01-27 result after updating all components. Refs: #1
2026-01-29 uses SPI2 instead of SPI in name. Refs: #1
2026-01-31 fixes incorrect SPI2 naming on switch sheets. Refs: #1
2026-01-31 removes 25M CLK input for switch. Refs: #1
2026-01-31 RGMII1 bus uses Microchip names. Refs: #1
2026-01-31 moves enable and IRQ GPIOs to PD0 to PD3 and reserves pins for I2S3. Refs: #1
2026-01-31 updates JTAG header naming etc. Refs: #1
2026-02-01 adds debug headers on STM side. Refs: #1
2026-02-01 adds footprint for VXM7. Refs: #1
2026-02-01 adds footprint for ferrite bead. Refs: #1
2026-02-01 aligns items to grid. Refs: #1
2026-02-01 updates component details for ordering. Refs: #1
2026-02-08 1: ading 0R on the JTAG TRST
2026-02-13 final clean up. Refs: #1
2026-02-13 moves 0R rail resistors for switch and controller to correct position. Refs: #1
2026-02-13 moves overseen 0R rail resistors to the correct place. Refs: #1
2026-02-14 1: adding JTAG header sheet name
2026-02-14 1: adding crystal sheet name
2026-02-14 1: adding controller sheet name
2026-02-22 initial commit for automatic current consumption calculation. Refs: #9
2026-02-22 adds Readme to describe helper scripts. Refs: #9
2026-02-22 adds dc/dc converters to current consumption. Refs: #9
2026-02-22 updates symbols and fixes ERC errors. Refs: #9
2026-02-22 adds green status LED to buck converters. Refs: #7
2026-02-23 adds green, orange and red LED to controller. Refs: #7
2026-02-25 refactors helper scripts. Refs: #11
2026-02-25 auto naming of the output file. Refs: #11
2026-02-25 updates to latest library. Refs: #13
2026-02-25 updates 0R resistor at +3V3 dc/dc converter. Refs: #13
2026-02-25 adds power connector. Refs: #8
2026-02-26 20: swapping RGMII port from RGMII1 to RGMII0
2026-02-28 updates LEDs. Refs: #7
2026-02-28 Introducing CERNL OHL v2 Strong
2026-02-28 6: adding net class for the SYNCE, PTP, MDI-X
2026-02-28 initial commit for SMA connector. WIP. Refs: #10
2026-02-28 clean up and fix on controller. Refs: #20
2026-02-28 updates footprints on separate branch in kebag_logic_libs. Refs: #24
2026-02-28 proper name for SMA connector. Refs: #10
2026-03-03 initial commit for mounting holes. WIP. Refs: #26
2026-03-03 towards a merge conflict free schematic. Refs: #9
2026-03-03 fixes footprints. Refs: #24
2026-03-03 adds mounting holes. Refs: #26
2026-03-03 fixes SMA footprint. Refs: #10
2026-03-03 updates footprints in kebag lib and fixes old reference in controller. Refs: #33
2026-03-07 Refs #29: fixing the rj45 dimension using inches instead of mm
2026-03-10 increases the courtyard distance for mounting holes. Refs: #26
2026-03-10 adds SMA connector to both PTP0 pins. Refs: #10
2026-03-10 updates 0R resistor to 0603. Refs: #31
2026-03-24 updates kicad library. Refs: #29
2026-03-24 updates footprints. Refs: #33
2026-03-24 removes unnecessary 0R resistors. Refs: #30
2026-03-24 updates components to latest library. Refs: #30
2026-03-27 updates RJ45 to latest version. Refs: #33
2026-04-16 updates lib to latest state. Refs: #41
2026-04-16 adds history folder to gitignore. Refs: #41
2026-04-16 open project in KiCAD10. Refs: #41
2026-04-16 updates components in shish-lan. Refs: #41
2026-04-16 updates switch. Refs: #41
2026-04-16 updates buck_1v15. Refs: #41
2026-04-16 updates buck_2v5. Refs: #41
2026-04-16 updates switch_gpios. Refs: #41
2026-04-16 updates switch_gpio_config. Refs: #41
2026-04-16 updates switch_power. Refs: #41
2026-04-16 updates switch_power_buffer_caps. Refs:#41
2026-04-16 updates switch_phys. Refs: #41
2026-04-16 updates RJ45_Connector_Port0. Refs: #41
2026-04-16 updates RJ45_Connector_Port1. Refs: #41
2026-04-16 updates RJ45_Connector_Port2. Refs: #41
2026-04-16 updates RJ45_Connector_Port3. Refs: #41
2026-04-16 updates buck_3v3. Refs: #41
2026-04-16 updates controller. Refs: #41
2026-04-16 updates jtag_header_arm. Refs: #41
2026-04-16 updates stm_dbg_header. Refs: #41
2026-04-16 updates crystal. Refs: #41
2026-04-16 updates project file. Refs: #41
2026-04-16 updates library. Refs: #41
2026-04-16 updates components in RJ45_Connector_Port0. Refs: #41
2026-04-16 updates components in switch. Refs: #41
2026-04-16 updates components in switch_gpios. Refs: #41
2026-04-17 initial commit for RJ45 header, mounting holes, power connectors, PPS, GND TP. Refs: #43
2026-04-19 shish-lan: pbc: adding proposition, movin sma and moving power, adding header as well
2026-05-11 updates 2u2 capacitors. Refs: #41
2026-05-11 updates 10pF capacitor. Refs: #41
2026-05-21 replaces 0402 100n caps with 0603 100n cap. Refs: #46
2026-05-21 updates lib. Refs: #46
2026-05-23 adds output jumper for +3V3. Refs: #49
2026-05-23 adds output jumper for +1V15. Refs: #49
2026-05-23 adds output jumper for +2V5. Refs: #49
2026-05-23 connects the shield pins to GND. Refs: #50
2026-05-23 replaces all capacitors with 10u. Refs: #52
2026-05-24 moves 0R resistor in front of buffering caps. Refs: #57
2026-05-24 moves all STM32 power behind the 0R resistor. Refs: #57
2026-05-24 puts switch power rails behind 0R resistor. Refs: #57
2026-05-29 layout v1
2026-05-29 update library submodule
2026-05-29 updates LCSC val.
2026-06-08 merges changes in the lib
